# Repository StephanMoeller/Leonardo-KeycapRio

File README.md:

# License: [CC BY-NC-SA 4.0](LICENSE)

v 0.8 (future)
- 1.6 mm black core pcb (pcbway), no solder mask on front, transparent solder mask on back side
- New cpu introduced: Kee Boar from Adafruit - surface mounting on the backside
- All routes are on the backside
- Thumb key position adjusted (no rotation angle between thumb keys)
- Tighter switch fittings
- Center reworked with better room for screws
- Diode pads a little smaller

# v 0.7
- 1.6 mm black solder mask (nextpcb)
- Only choc v1 (more snappy center hole)
- Reworked center area and screws
- Top plate included
- 1.6 mm pcb (1.2 mm previously) for easier soldering as the hotswap sockets' pins were taller than 1.2 mm.
- Ordered at nextpcb (black matte) to test out another vendors ("interpretation of") black

# v 0.6:
- 1.2 mm black solder mask (jlcpcb)
- Extra pinky key
- Extra thumb key
- Adjuated screw hole positions

# v 0.5:
- Choc only (v1+v2)
- Choc spaced between rows, mx spaced between columns (except inner column that is 18mm spaced)

# v 0.4:
- MiniMelf diodes
- 1mm pcb (previous was 1.6mm but the pla tenting solution started to bend)
- 2 versions: 1 for mx, 1 for choc v1 and v2 (on the same pcb)
- All screws are on the outside now to be able to mount/unmount without having to remove any switches

# v 0.3:
- M3 screw holes for mounting instead of press fitting into a case
- More tight mx footprint for better fixation of the switches

# V 0.2:
- Created with custom kicad generator
- Even traces through the squiggle for a more finished look

# V 0.1:
- Created with ergogen

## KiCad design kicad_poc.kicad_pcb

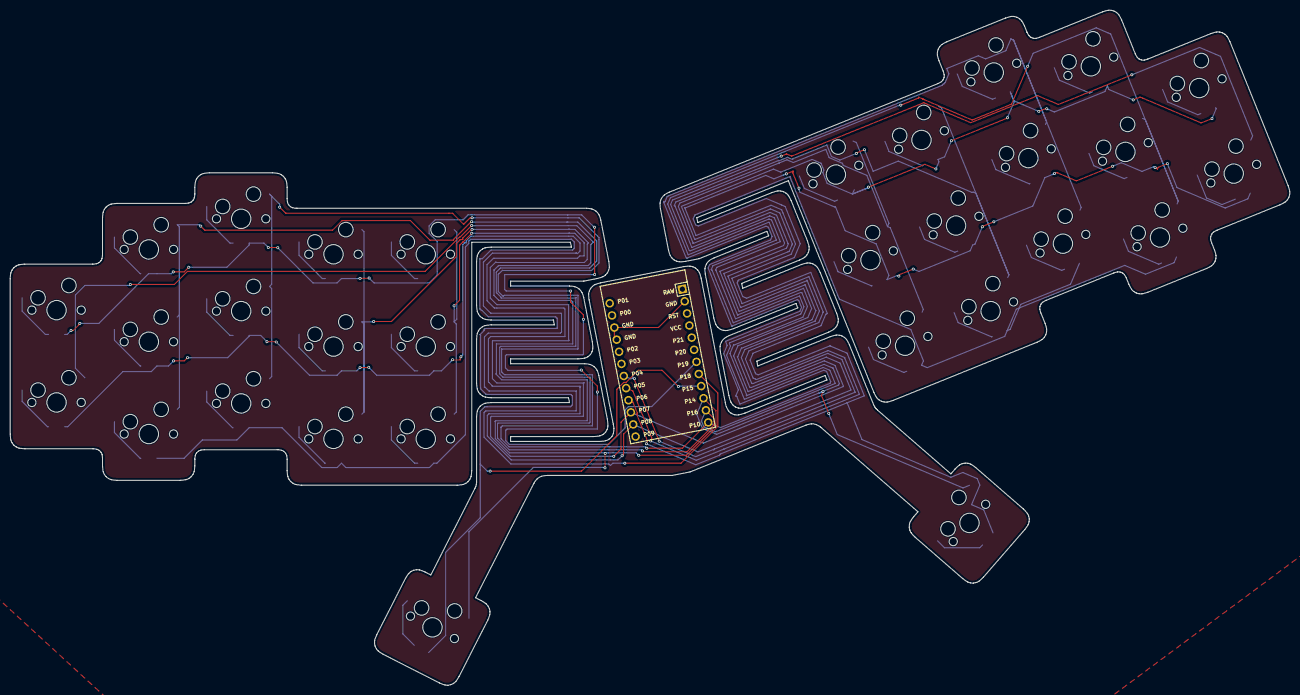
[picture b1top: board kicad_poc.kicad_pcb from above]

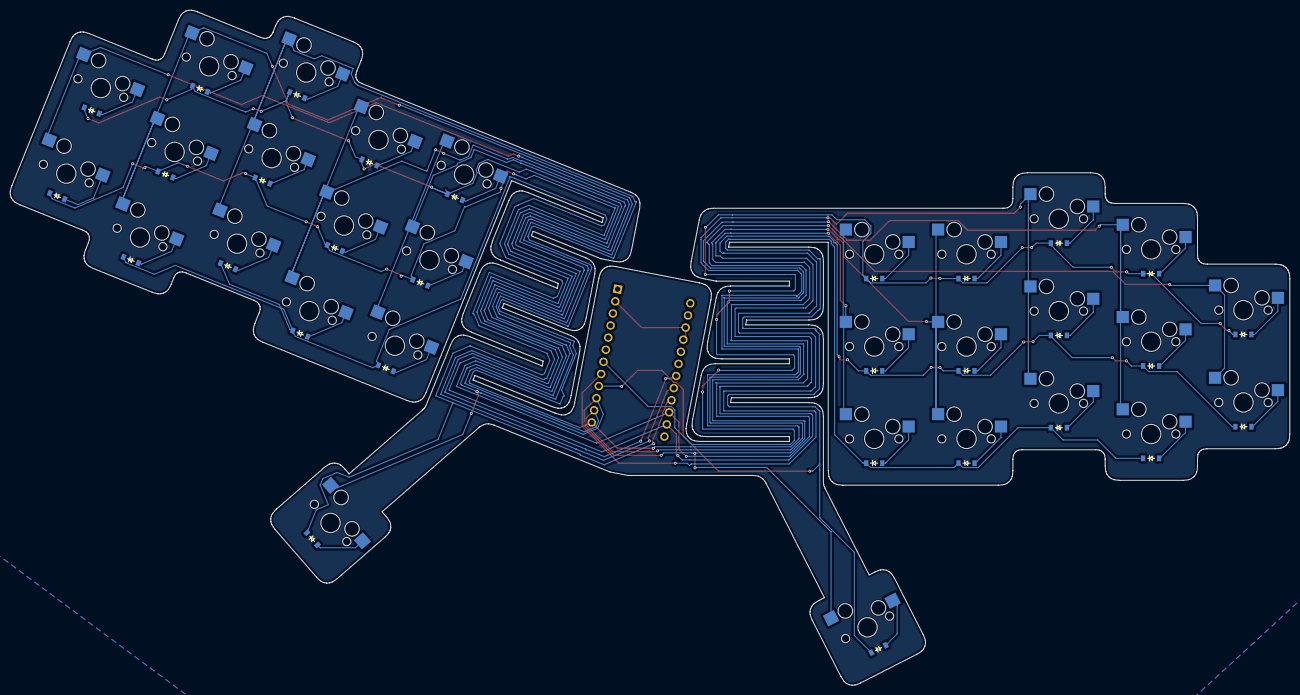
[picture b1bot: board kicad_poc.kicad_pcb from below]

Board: 2 copper layers, 263.4 x 138.9 mm, 61 parts (30 on the bottom side), 42 nets.

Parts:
D1, D2, D3, D4, D5, D6, D7, D8, D9, D10, D11, D12, D13, D14, D15, D16, D17, D18, D19, D20, D21, D22, D23, D24, D25, D26, D27, D28, D29, D30: diode_tht_sod123
MCU1: ProMicro
S1, S2, S3, S4, S5, S6, S7, S8, S9, S10, S11, S12, S13, S14, S15, S16, S17, S18, S19, S20, S21, S22, S23, S24, S25, S26, S27, S28, S29, S30: MX

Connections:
GND: MCU1.2, MCU1.15, MCU1.16
P4: D17.1, D20.1, D23.1, D26.1, D29.1, MCU1.19
P5: D16.1, D19.1, D22.1, D25.1, D28.1, MCU1.20
P6: D18.1, D21.1, D24.1, D27.1, D30.1, MCU1.21
P7: MCU1.22, S9.2, S10.2, S11.2, S24.2, S25.2, S26.2
P8: MCU1.23, S12.2, S13.2, S14.2, S27.2, S28.2, S29.2
P10: MCU1.12, S6.2, S7.2, S8.2, S21.2, S22.2, S23.2
P14: MCU1.10, S1.2, S2.2, S15.2, S16.2, S17.2, S30.2
P15: D3.1, D6.1, D9.1, D12.1, D15.1, MCU1.9
P16: MCU1.11, S3.2, S4.2, S5.2, S18.2, S19.2, S20.2
P18: D1.1, D4.1, D7.1, D10.1, D13.1, MCU1.8
P19: D2.1, D5.1, D8.1, D11.1, D14.1, MCU1.7
center_single: D15.2, S15.1
index_bottom: D9.2, S9.1
index_home: D10.2, S10.1
index_top: D11.2, S11.1
inner_bottom: D12.2, S12.1
inner_home: D13.2, S13.1
inner_top: D14.2, S14.1
middle_bottom: D6.2, S6.1
middle_home: D7.2, S7.1
middle_top: D8.2, S8.1
mirror_center_single: D30.2, S30.1
mirror_index_bottom: D24.2, S24.1
mirror_index_home: D25.2, S25.1
mirror_index_top: D26.2, S26.1
mirror_inner_bottom: D27.2, S27.1
mirror_inner_home: D28.2, S28.1
mirror_inner_top: D29.2, S29.1
mirror_middle_bottom: D21.2, S21.1
mirror_middle_home: D22.2, S22.1
mirror_middle_top: D23.2, S23.1
mirror_pinky_home: D16.2, S16.1
mirror_pinky_top: D17.2, S17.1
mirror_ring_bottom: D18.2, S18.1
mirror_ring_home: D19.2, S19.1
mirror_ring_top: D20.2, S20.1
pinky_home: D1.2, S1.1
pinky_top: D2.2, S2.1
ring_bottom: D3.2, S3.1
ring_home: D4.2, S4.1
ring_top: D5.2, S5.1

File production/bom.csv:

Designator,Footprint,Quantity,Value,LCSC Part #
"D1, D10, D11, D12, D13, D14, D15, D16, D17, D18, D19, D2, D20, D21, D22, D23, D24, D25, D26, D27, D28, D29, D3, D30, D4, D5, D6, D7, D8, D9",diode_tht_sod123,30,,
MCU1,ProMicro,1,,
"S1, S10, S11, S12, S13, S14, S15, S16, S17, S18, S19, S2, S20, S21, S22, S23, S24, S25, S26, S27, S28, S29, S3, S30, S4, S5, S6, S7, S8, S9",MX,30,,

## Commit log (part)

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2026-04-10 all files
2026-04-10 working state - imported pcb and outline, before doing routes
2026-04-10 added simple single side routings on both sides
2026-04-10 latest with a working dxf
2026-04-10 working state before vias
2026-04-10 each side routed
2026-04-10 all pcb wiring done!
2026-04-13 latest - sent to the jlc
2026-06-15 moved everything inside a v0.1 folder
2026-06-15 added v0.2
2026-06-15 Add version images to README.md
2026-06-18 Update README with improvements and next steps
2026-06-22 added a v3
2026-06-22 added stl case
2026-06-22 Update README with images and design changes
    Added multiple images and updated the 'What's new?' section with details about design changes.
2026-06-22 Update README with new images and design details
    Added images and updated the 'What's new?' section with design changes.
2026-06-22 Update README with v0.3 changes
    Added details about M3 screw holes and tighter MX footprint.
2026-06-23 added v0.4
2026-06-23 more readme
2026-06-29 added and rearranged pcbs
2026-06-29 added stl for tenting
